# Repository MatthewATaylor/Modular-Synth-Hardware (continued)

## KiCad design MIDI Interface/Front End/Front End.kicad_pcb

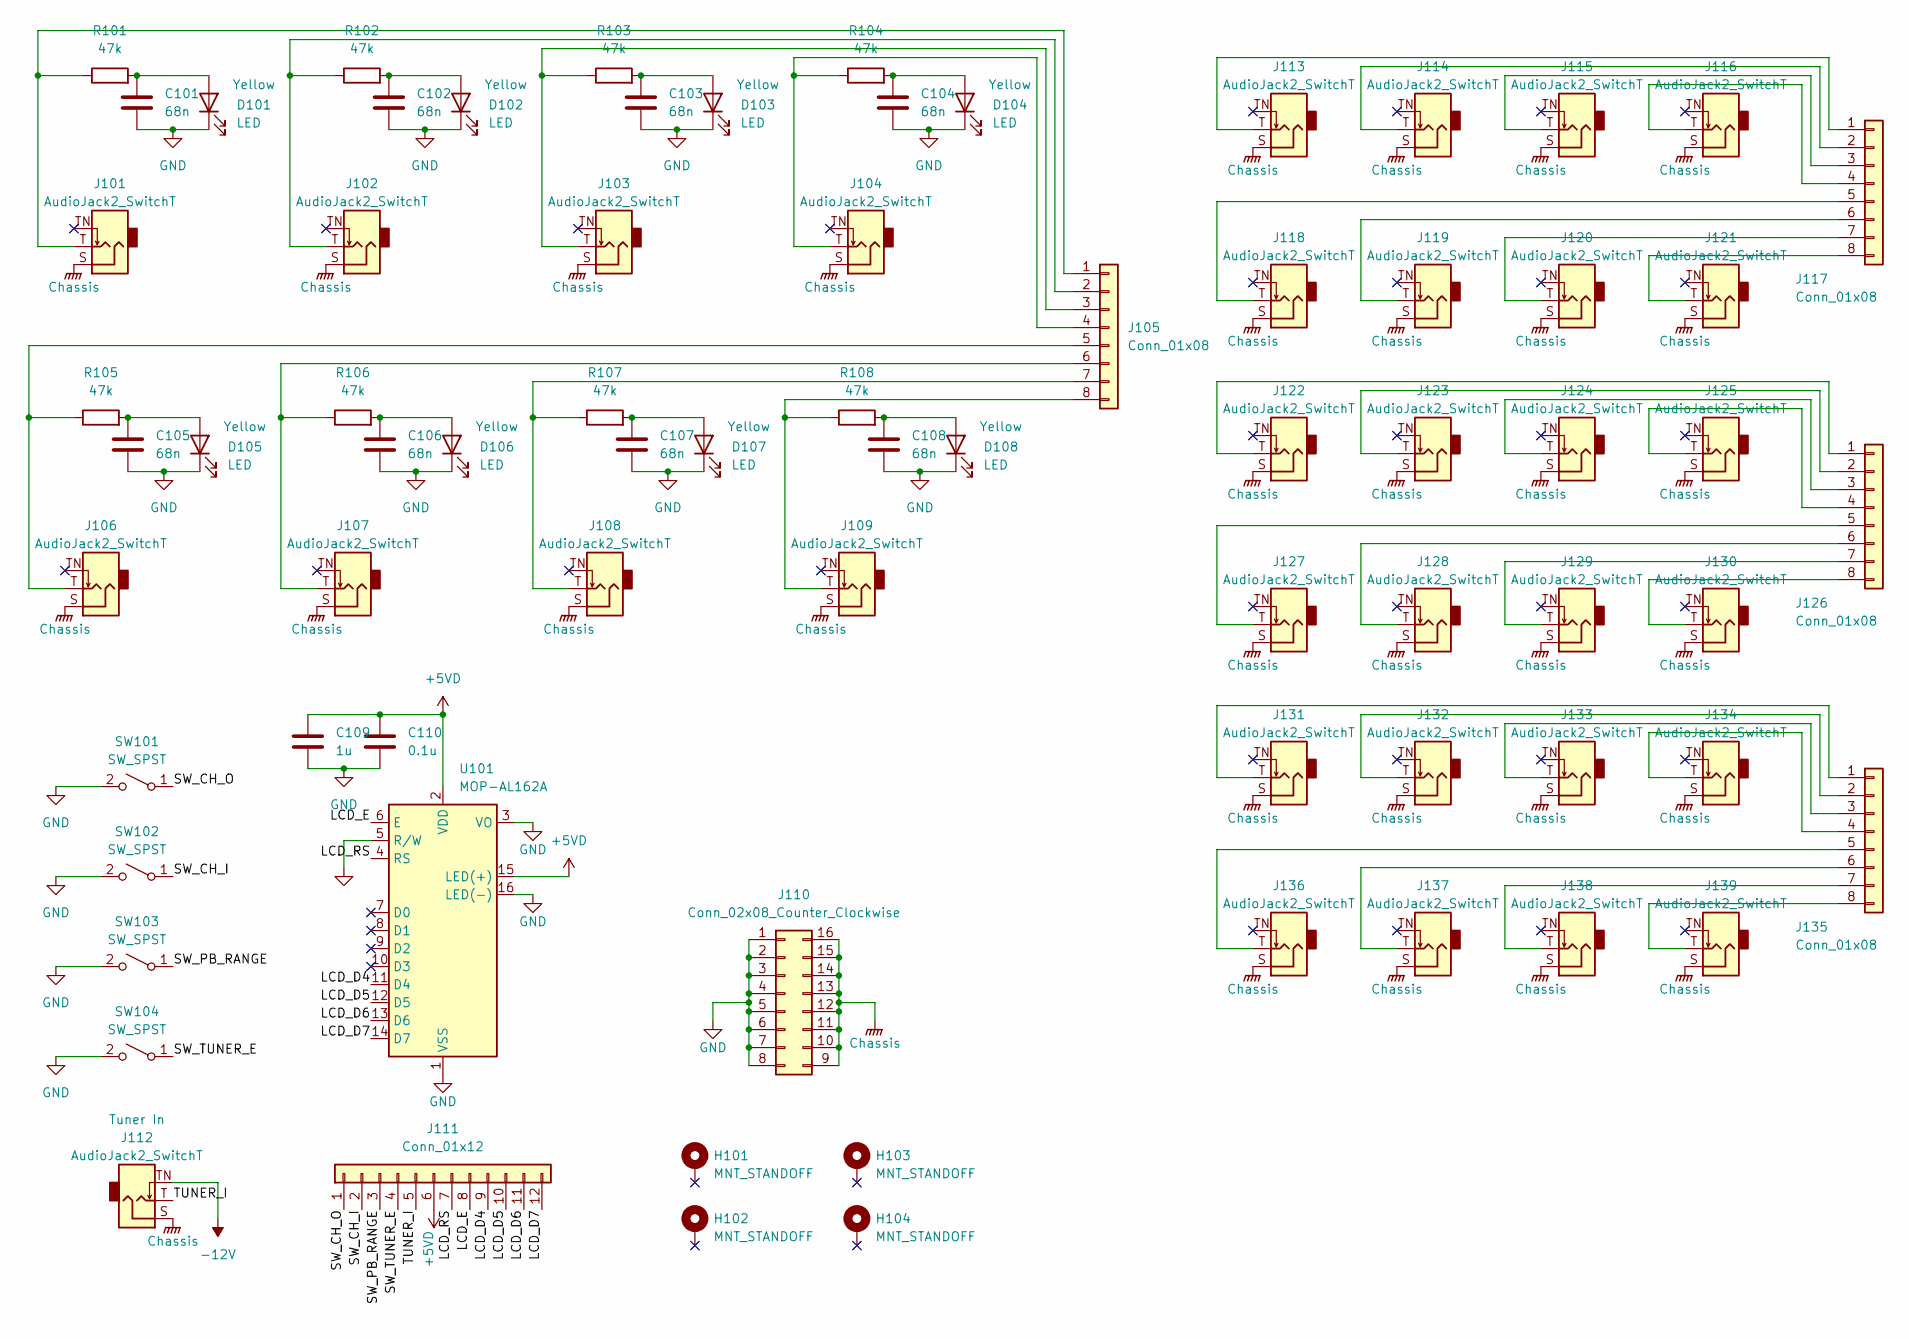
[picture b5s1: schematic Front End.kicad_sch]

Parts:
C101, C102, C103, C104, C105, C106, C107, C108: 68n; C_Disc_D5.5mm_W2.5mm_P2.50mm
C109: 1u; C_Disc_D5.5mm_W4.0mm_P2.50mm
C110: 0.1u; C_Disc_D5.5mm_W2.5mm_P2.50mm
D101, D102, D103, D104, D105, D106, D107, D108: LED; LED_D5.0mm
H101, H102, H103, H104: MNT_STANDOFF; MountingHole_Pitch7.5mm_Drill3.4mm
J101, J102, J103, J104, J106, J107, J108, J109, J112, J113, J114, J115, J116, J118, J119, J120, J121, J122, J123, J124, J125, J127, J128, J129, J130, J131, J132, J133, J134, J136, J137, J138, J139: AudioJack2_SwitchT; Jack_3.5mm_QingPu_WQP-PJ398SM_Vertical_CircularHoles
J105, J117, J126, J135: Conn_01x08; PinSocket_1x08_P2.54mm_Vertical
J110: Conn_02x08_Counter_Clockwise; PinSocket_2x08_P2.54mm_Vertical
J111: Conn_01x12; PinSocket_1x12_P2.54mm_Vertical
R101, R102, R103, R104, R105, R106, R107, R108: 47k; R_Axial_DIN0207_L6.3mm_D2.5mm_P7.62mm_Horizontal
SW101, SW102, SW103, SW104: SW_SPST; PBS-105
U101: MOP-AL162A; WC1602A_Outline

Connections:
+5VD: C109.1, C110.1, J111.6, U101.2 (VDD), U101.15 (LED(+))
-12V: J112.TN
/LCD_D4: J111.9, U101.11 (D4)
/LCD_D5: J111.10, U101.12 (D5)
/LCD_D6: J111.11, U101.13 (D6)
/LCD_D7: J111.12, U101.14 (D7)
/LCD_E: J111.8, U101.6 (E)
/LCD_RS: J111.7, U101.4 (RS)
/SW_CH_I: J111.2, SW102.1 (A)
/SW_CH_O: J111.1, SW101.1 (A)
/SW_PB_RANGE: J111.3, SW103.1 (A)
/SW_TUNER_E: J111.4, SW104.1 (A)
/TUNER_I: J111.5, J112.T
Chassis: J101.S, J102.S, J103.S, J104.S, J106.S, J107.S, J108.S, J109.S, J110.9, J110.10, J110.11, J110.12, J110.13, J110.14, J110.15, J110.16, J112.S, J113.S, J114.S, J115.S, J116.S, J118.S, J119.S, J120.S, J121.S, J122.S, J123.S, J124.S, J125.S, J127.S, J128.S, J129.S, J130.S, J131.S, J132.S, J133.S, J134.S, J136.S, J137.S, J138.S, J139.S
GND: C101.1, C102.1, C103.1, C104.1, C105.1, C106.1, C107.1, C108.1, C109.2, C110.2, D101.1 (K), D102.1 (K), D103.1 (K), D104.1 (K), D105.1 (K), D106.1 (K), D107.1 (K), D108.1 (K), J110.1, J110.2, J110.3, J110.4, J110.5, J110.6, J110.7, J110.8, SW101.2 (B), SW102.2 (B), SW103.2 (B), SW104.2 (B), U101.1 (VSS), U101.3 (VO), U101.5 (R/W), U101.16 (LED(-))
unnamed: C101.2, D101.2 (A), R101.2
unnamed: C102.2, D102.2 (A), R102.2
unnamed: C103.2, D103.2 (A), R103.2
unnamed: C104.2, D104.2 (A), R104.2
unnamed: C105.2, D105.2 (A), R105.2
unnamed: C106.2, D106.2 (A), R106.2
unnamed: C107.2, D107.2 (A), R107.2
unnamed: C108.2, D108.2 (A), R108.2
unnamed: J101.T, J105.1, R101.1
unnamed: J102.T, J105.2, R102.1
unnamed: J103.T, J105.3, R103.1
unnamed: J104.T, J105.4, R104.1
unnamed: J105.5, J106.T, R105.1
unnamed: J105.6, J107.T, R106.1
unnamed: J105.7, J108.T, R107.1
unnamed: J105.8, J109.T, R108.1
unnamed: J113.T, J117.1
unnamed: J114.T, J117.2
unnamed: J115.T, J117.3
unnamed: J116.T, J117.4
unnamed: J117.5, J118.T
unnamed: J117.6, J119.T
unnamed: J117.7, J120.T
unnamed: J117.8, J121.T
unnamed: J122.T, J126.1
unnamed: J123.T, J126.2
unnamed: J124.T, J126.3
unnamed: J125.T, J126.4
unnamed: J126.5, J127.T
unnamed: J126.6, J128.T
unnamed: J126.7, J129.T
unnamed: J126.8, J130.T
unnamed: J131.T, J135.1
unnamed: J132.T, J135.2
unnamed: J133.T, J135.3
unnamed: J134.T, J135.4
unnamed: J135.5, J136.T
unnamed: J135.6, J137.T
unnamed: J135.7, J138.T
unnamed: J135.8, J139.T

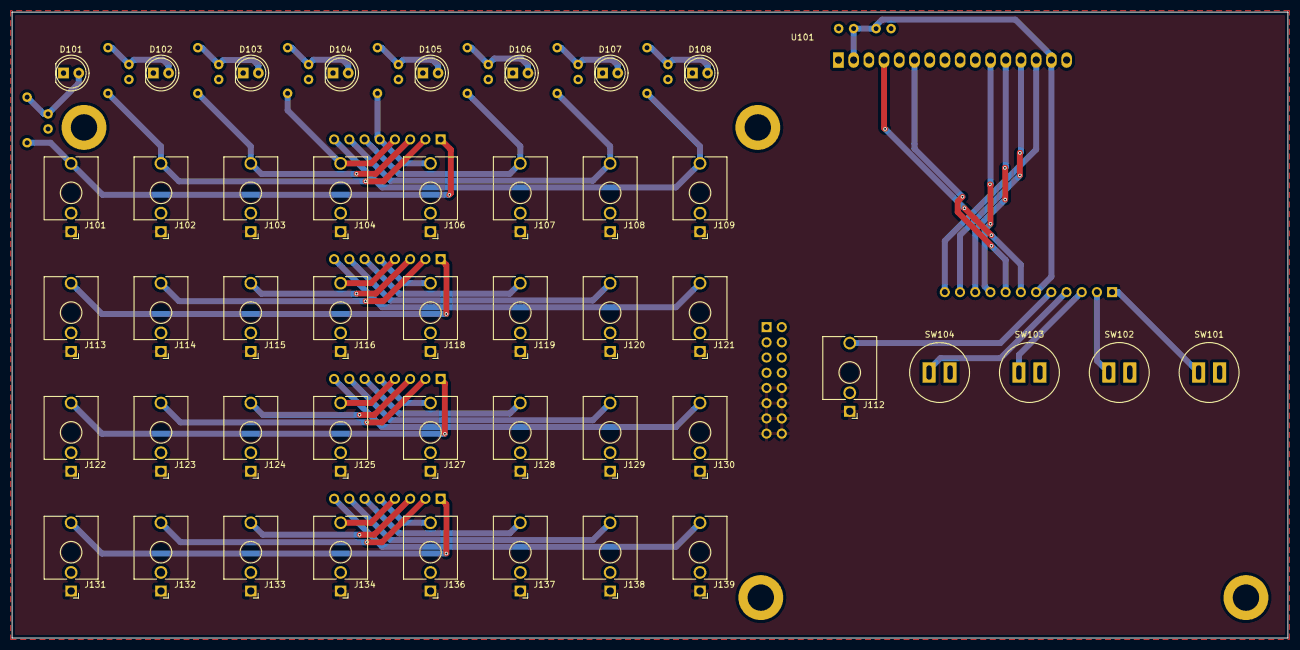
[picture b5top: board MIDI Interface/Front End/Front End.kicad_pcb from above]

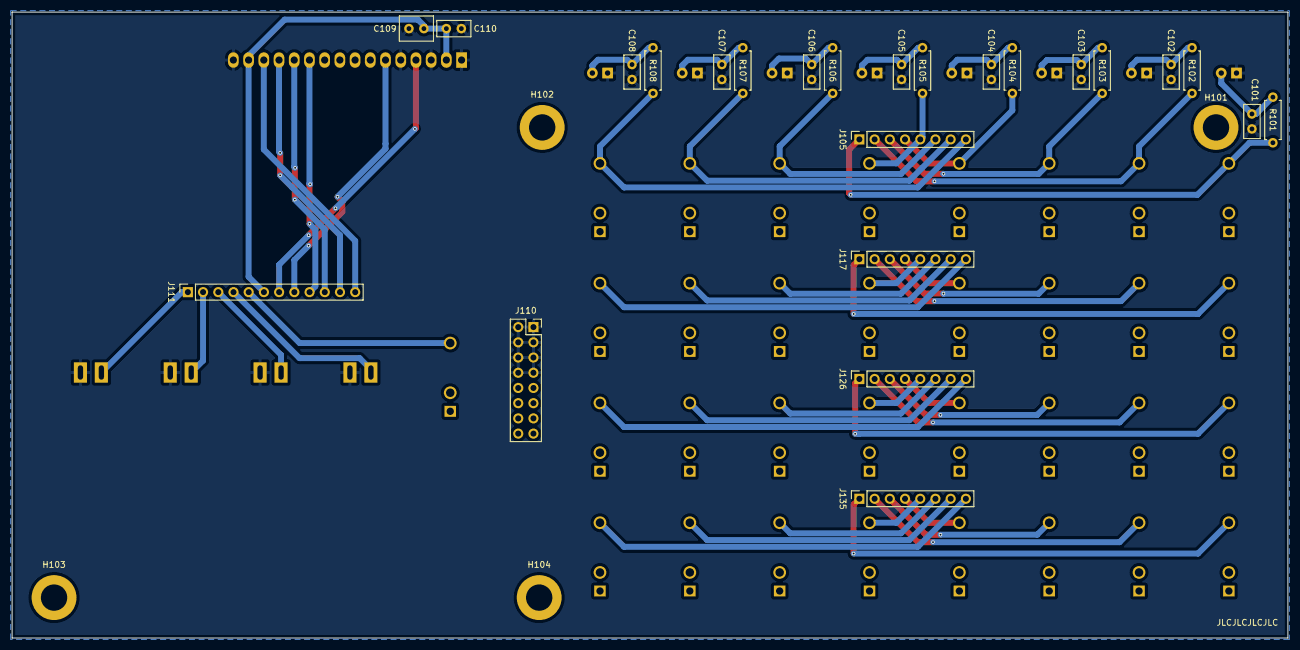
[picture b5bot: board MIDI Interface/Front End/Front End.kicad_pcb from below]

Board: 2 copper layers, 213.0 x 104.5 mm, 74 parts (28 on the bottom side), 54 nets.
